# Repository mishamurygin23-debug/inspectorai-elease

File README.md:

# Инспектор ИИ — Стройнадзор Москвы

> **Интеллектуальная система автоматического контроля проектных решений, отслеживания изменений между стадиями проектирования (ПД, РД) и верификации исполнительной документации (ИД) по 132 параметрам Мосгосстройнадзора.**
> 
> *Решение разработано в рамках Задачи №10 для Комитета государственного строительного надзора города Москвы (Мосгосстройнадзор).*

---

## 📌 Содержание
1. [О проекте и назначение системы](#-о-проекте-и-назначение-системы)
2. [Ключевые возможности и функциональные модули](#-ключевые-возможности-и-функциональные-модули)
3. [Архитектура решения](#-архитектура-решения)
4. [Матрица 132 параметров контроля](#-матрица-132-параметров-контроля)
5. [ML-модели и пайплайн дообучения](#-ml-модели-и-пайплайн-дообучения)
6. [Интеграция с ИАС РИН и подписание УКЭП](#-интеграция-с-иас-рин-и-подписание-укэп)
7. [Ролевая модель доступа (RBAC)](#-ролевая-модель-доступа-rbac)
8. [Установка и запуск](#-установка-и-запуск)
9. [Структура проекта](#-структура-проекта)
10. [Сценарий работы инспектора (Quick Start)](#-сценарий-работы-инспектора-quick-start)

---

## 🏢 О проекте и назначение системы

При строительстве объектов капитального строительства в Москве возникает критический разрыв между:
1. **Проектной документацией (ПД)**, прошедшей государственную экспертизу (Мосгосэкспертиза);
2. **Рабочей документацией (РД)**, по которой генподрядчик непосредственно ведёт строительно-монтажные работы на площадке;
3. **Исполнительной документацией (ИД)** — актами освидетельствования скрытых работ (АОСР), исполнительными геодезическими схемами и паспортами материалов.

Несогласованные изменения (самовольное изменение марок бетона, уменьшение сечений арматуры, перенос несущих перегородок, изменение габаритов эвакуационных выходов) несут прямую угрозу конструктивной надежности и пожарной безопасности.

**«Инспектор ИИ»** автоматизирует труд государственного строительного инспектора, мгновенно находя расхождения и формируя юридически выверенные акты проверок и предписания с привязкой к нормативной базе (СП, ГОСТ, ПП РФ № 87, Градостроительный кодекс РФ).

---

## ✨ Ключевые возможности и функциональные модули

### 1. 📊 Мониторинг и Дашборд объектов (`Dashboard`)
- Централизованный обзор строящихся объектов Москвы с присвоением риск-статуса (**Зелёный**, **Жёлтый**, **Красный**).
- Сводная аналитика нарушений по категориям критичности (Критические, Значительные, Незначительные).
- Воронка обработки параметров: *Всего проверено -> Подтвержденные нарушения -> Кандидаты -> Норма подтверждена -> Требует пояснений*.

### 2. 🔍 Инспекционное рабочее пространство (`InspectionWorkspace`)
- **Двухоконный и трехоконный сравнительный просмотр** документов (ПД vs РД vs ИД).
- **Интерактивный Bounding Box / Overlay**: подсвечивание точных фрагментов чертежей и спецификаций с визуализацией расхождений.
- **Инструменты верификации инспектора**:
  - Принятие замечания (`Подтвердить нарушение`).
  - Отклонение с обязательным указанием нормативного кода причины:
    - `WRONG_REVISION` — Сравнение с неактуальной ревизией листа;
    - `APPROVED_CHANGE` — Согласованное изменение (лист согласования/разрешение на изменение);
    - `OCR_ERROR` — Ошибка оптического распознавания текста;
    - `ALIGNMENT_ERROR` — Ошибка совмещения слоев/осей;
    - `PARAMETER_NOT_APPLICABLE` — Параметр не применимым к данному конструктиву;
    - `EXCEED_TOLERANCE_ACCEPTABLE` — Отклонение в пределах допустимых допусков по СП;
    - `OTHER` — Иная обоснованная причина.

### 3. 📐 Парсинг штампов и чертежей (`DrawingParserTab`)
- Автоматическое распознавание основной надписи (штампа) по **ГОСТ Р 21.101-2020** (шифр объекта, раздел, стадия, номер листа, ревизия, фамилии разработчиков, ГИП).
- Определение масштаба, координатных осей и слоёв чертежей.
- Автоматическая классификация загружаемых документов (ПД, РД, ИД) на основе текстовых и графических признаков с точностью >98%.

### 4. 🧠 Генератор гипотез и коллизий (`HypothesisTab`)
- Интеллектуальный поиск скрытых коллизий методами:
  - **Логический анализ связей** (например, диаметр арматуры в КР vs спецификация);
  - **Семантический диссонанс** (расхождения в текстовых указаниях ПЗ и чертежах АР/КР);
  - **Нормативный аудит** (проверка на соответствие СП 63.13330, СП 16.13330, СП 1.13130, СП 118.13330);
  - **ML-паттерны** (предсказание типичных мест фальсификаций и ошибок генподрядчиков).
- Интерактивный конструктор гипотез для быстрого добавления инспектором новых проверочных шаблонов.

### 5. 📑 Реестр исполнительной документации (`ExecutiveDocumentationRegistry`)
- Электронный учет актов освидетельствования скрытых работ (АОСР) по РД-11-02-2006 / Приказу Минстроя № 344/пр.
- Контроль наличия геодезических исполнительных схем и паспортов/сертификатов на материалы (бетон, арматура, сэндвич-панели).
- Двусторонняя проверка: сверка объемов и дат в АОСР с общим журналом работ (РД-11-05-2007) и проектом.

### 6. 🏛 Интеграция с ИАС РИН Мосгосстройнадзора (`IaisRinTab`)
- Прямая синхронизация с **Информационно-аналитической системой управления контрольно-надзорной деятельностью (ИАС РИН)**.
- Формирование структурированных пакетов данных проверки (JSON/XML).
- Подписание актов проверки и предписаний **Усиленной квалифицированной электронной подписью (УКЭП)** инспектора по стандарту **ГОСТ Р 34.10-2012 / ГОСТ Р 34.11-2012**.

### 7. 🤖 ML-репозиторий и дообучение моделей (`MLRepositoryTab`, `MLRetrainingTab`)
- Управление версиями весов специализированных моделей (текущий рабочий чекпоинт `v2.4.2-altufievo-finetuned`).
- Формирование «Золотого датасета» (Gold Standard Ground Truth) на основе вердиктов экспертов-инспекторов.
- Пайплайн запуска дообучения (`fine_tune_pipeline.py`) с отслеживанием метрик в реальном времени.

### 8. 🛡 Неизменяемый журнал аудита WORM (`AuditLogTab`)
- Принцип **Write Once, Read Many (WORM)** для исключения фальсификации результатов проверок.
- Фиксация каждого действия (загрузка файла, подтверждение/отклонение замечания, подписание УКЭП, экспорт).
- Формирование криптографических хешей записей аудита для гарантии неизменности истории.

---

## 🏛 Архитектура решения

```
┌────────────────────────────────────────────────────────────────────────┐
│                   ФРОНТЕНД-ПРИЛОЖЕНИЕ (React 19 + TypeScript)          │
│                                                                        │
│  ┌──────────────┐  ┌──────────────────┐  ┌───────────────────────────┐ │
│  │  Дашборд     │  │  Инспекционное   │  │  Матрица 132 параметров   │ │
│  │  объектов    │  │  пространство    │  │  (ПП РФ № 87, СП, ГОСТ)   │ │
│  └──────┬───────┘  └─────────┬────────┘  └─────────────┬─────────────┘ │
│         │                    │                         │               │
│  ┌──────┴───────┐  ┌─────────┴────────┐  ┌─────────────┴─────────────┐ │
│  │ Парсер ГОСТ  │  │ Двухоконный PDF- │  │  Реестр ИД (АОСР, схемы,  │ │
│  │ штампов / CAD│  │ вьювер с BBox    │  │  лабораторные паспорта)   │ │
│  └──────┬───────┘  └─────────┬────────┘  └─────────────┬─────────────┘ │
│         │                    │                         │               │
│  ┌──────┴────────────────────┴─────────────────────────┴─────────────┐ │
│  │          Слой бизнес-логики и верификации нарушений               │ │
│  └──────┬────────────────────┬─────────────────────────┬─────────────┘ │
└─────────┼────────────────────┼─────────────────────────┼───────────────┘
          │                    │                         │
          ▼                    ▼                         ▼
┌──────────────────┐ ┌──────────────────┐ ┌──────────────────────────────┐
│  AI / ML Модуль  │ │   Криптография   │ │       Интеграция ИАС РИН     │
│  - OCR & Layout  │ │   и WORM-Аудит   │ │       Мосгосстройнадзора     │
│  - Cross-Doc Link│ │ - УКЭП           │ │ - Экспорт пакета проверки    │
│  - Поиск коллизий│ │   ГОСТ 34.10-2012│ │ - Синхронизация статусов     │
│  - Fine-tuning   │ │ - Хеш-цепочка    │ │ - Выгрузка предписаний в PDF │
└──────────────────┘ └──────────────────┘ └──────────────────────────────┘
```

---

## 📋 Матрица 132 параметров контроля

Система контролирует документацию по 132 утверждённым параметрам, сгруппированным по обязательным разделам проектной документации (согласно **Постановлению Правительства РФ № 87**):

| Шифр раздела | Наименование раздела ПД | Кол-во параметров | Примеры контролируемых параметров | Нормативная база |
|--------------|-------------------------|-------------------|-----------------------------------|-------------------|
| **ПЗ** | Пояснительная записка | 8 | ТЭПы, площадь застройки, этажность, класс энергоэффективности | ПП РФ № 87, СП 118.13330 |
| **СПЗУ** | Схема планировочной организации земельного участка | 12 | Границы ГПЗУ, красные линии, процент застройки, проезды МЧС | СП 42.13330, СП 4.13130 |
| **АР** | Архитектурные решения | 24 | Высотные отметки, ширина коридоров и выходов, огнестойкость ограждений | СП 54.13330, СП 1.13130 |
| **КР** | Конструктивные решения | 28 | Класс бетона, диаметр/шаг рабочей арматуры, глубина заложения свай | СП 63.13330, СП 22.13330 |
| **ИОС 1–5** | Инженерные сети (ЭОМ, ВК, ОВ, СС, ТС) | 32 | Нагрузки кВт, расходы воды, воздухообмен, пожаротушение, категории надежности | СП 30, 31, 60, 10, 134 |
| **ПОС / ПОД**| Проект организации строительства / сноса | 10 | Опасные зоны кранов, бытовой городок, мойка колес, стройгенплан | СП 48.13330 |
| **ППМ** | Мероприятия пожарной безопасности | 10 | Категории по взрывопожароопасности, противопожарные преграды | ФЗ № 123-ФЗ, СП 2.13130 |
| **ОДИ** | Доступность для маломобильных групп | 8 | Уклоны пандусов, ширина дверей, тактильные полосы, лифты | СП 59.13330.2020 |

Полная интерактивная таблица с формулами сопоставления, порогами допусков и источниками данных доступна во вкладке **«Матрица 132 параметров»**.

---

## 🧠 ML-модели и пайплайн дообучения

В состав системы входит специализированная мультимодальная архитектура для анализа строительной документации:
- **Детекция и извлечение таблиц и штампов:** Выделение зон основных надписей по ГОСТ 21.101-2020.
- **Cross-Document Entity Linking:** Связывание позиций между ведомостями расхода стали, планами армирования и паспортами качества свай.
- **Модель детекции нарушений (`inspector_hypothesis_v2.4`):**
  - Обучена и валидирована на реальном комплекте документации г. Москвы (*Торговое здание, Алтуфьевское шоссе, вл. 79Б, стр. 1*).
  - **Character Accuracy (OCR):** 98.8%
  - **Exact Match (марки материалов):** 95.2%
  - **BBox IoU (точность локализации):** 97.2%
  - **Precision:** 98.2%
  - **Recall:** 94.5%
  - **Интегральный F1-score:** 96.8%

Запуск переобучения пайплайна:
```bash
python ml_models/inspector_hypothesis_v2.4/fine_tune_pipeline.py --epochs 5 --dataset dataset_altufievo_ground_truth.json
```

---

## 🔒 Интеграция с ИАС РИН и подписание УКЭП

1. **Формирование дела проверки:** Агрегация всех подтвержденных инспектором нарушений, доказательных фрагментов (BBox-полигонов) и ссылок на листы ПД/РД/ИД.
2. **Криптографическое подписание:**
   - Поддерживаются сертификаты квалифицированной электронной подписи по стандартам **ГОСТ Р 34.10-2012** (длина ключа 256/512 бит) и **ГОСТ Р 34.11-2012**.
   - Формирование отсоединенной или присоединенной подписи (форматы CMS/CAdES-BES).
3. **Шлюз взаимодействия с ИАС РИН:**
   - Передача пакета через защищенный REST/SOAP API с присвоением входящего номера и трекингом статуса проверки в режиме онлайн.

---

## 👥 Ролевая модель доступа (RBAC)

Система поддерживает 4 базовые роли с разграничением прав:
1. **Инспектор Мосгосстройнадзора (`INSPECTOR`):**
   - Загрузка проектной, рабочей и исполнительной документации.
   - Проведение проверок, верификация гипотез (подтверждение/отклонение нарушений).
   - Подписание предписаний личной УКЭП.
2. **Супервайзер / Начальник управления (`SUPERVISOR`):**
   - Контроль работы подведомственных инспекторов.
   - Утверждение предписаний высокой степени опасности.
   - Сквозной мониторинг строительных объектов Москвы.
3. **ML-инженер / Аналитик данных (`ML_ENGINEER`):**
   - Мониторинг метрик распознавания и детекции коллизий.
   - Формирование эталонных выборок и запуск дообучения моделей.
   - Управление репозиторием чекпоинтов.
4. **Администратор системы (`ADMIN`):**
   - Управление справочниками нормативной базы (СП, ГОСТ, приказы).
   - Настройка интеграций с ИАС РИН.
   - Контроль целостности WORM-журнала аудита.

---

## 🚀 Установка и запуск

### Системные требования
- **Node.js:** версия 18.0 или выше (рекомендуется 20 LTS)
- **Менеджер пакетов:** npm, pnpm или bun
- **Python (для ML-пайплайна дообучения):** 3.10+ с установленными `torch`, `transformers`

### Пошаговая инструкция

1. **Клонирование репозитория:**
   ```bash
   git clone <URL_РЕПОЗИТОРИЯ>
   cd inspector-ai-stroynadzor
   ```

2. **Установка зависимостей фронтенда:**
   ```bash
   npm install
   ```

3. **Запуск сервера разработки:**
   ```bash
   npm run dev
   ```
   Приложение откроется по адресу `http://localhost:3000`.

4. **Проверка типов и линтинг:**
   ```bash
   npm run lint
   ```

5. **Сборка для промышленного развертывания (Production build):**
   ```bash
   npm run build
   ```
   Собранное статическое приложение размещается в каталоге `dist/`.

6. **Предпросмотр production-сборки:**
   ```bash
   npm run preview
   ```

---

## 📂 Структура проекта

```
.
├── index.html                   # HTML-шаблон с метаданными и шрифтами
├── package.json                 # Зависимости и npm-скрипты (Vite, React 19, Tailwind CSS)
├── vite.config.ts               # Конфигурация сборщика Vite
├── tsconfig.json                # Параметры компилятора TypeScript
├── metadata.json                # Метаданные приложения и права доступа
├── ml_models/                   # Репозиторий весов и скриптов ML-моделей
│   └── inspector_hypothesis_v2.4/
│       ├── config.json          # Параметры архитектуры нейросети
│       ├── dataset_altufievo_ground_truth.json # Размеченный золотой датасет
│       ├── fine_tune_pipeline.py # Скрипт дообучения
│       ├── model_metadata.json  # Метрики точности и версии
│       └── README.md            # Отчет по валидации модели
├── docs/                        # Расширенная техническая документация
│   ├── ARCHITECTURE.md          # Детальная архитектура и потоки данных
│   ├── USER_GUIDE.md            # Руководство пользователя для инспекторов
│   └── API_AND_INTEGRATION.md   # Спецификация обмена с ИАС РИН
└── src/
    ├── main.tsx                 # Точка входа React
    ├── App.tsx                  # Главный компонент, роутинг вкладок и глобальное состояние
    ├── index.css                # Глобальные стили Tailwind CSS
    ├── types/                   # TypeScript интерфейсы и типы данных
    │   ├── index.ts             # Типы объектов, проверок, гипотез, статусов
    │   └── sectionsRegistry.ts  # Реестр разделов ПП РФ № 87
    ├── data/                    # Базы данных и справочники
    │   ├── matrix132.ts         # Матрица 132 параметров Мосгосстройнадзора
    │   ├── mockData.ts          # Демонстрационные объекты, протоколы и логи
    │   ├── comprehensiveHypothesesData.ts # База типовых нарушений и коллизий
    │   └── rolesData.ts         # Профили пользователей и уровни доступа
    ├── components/              # Реакт-компоненты модулей системы
    │   ├── Navbar.tsx           # Верхняя панель навигации и переключение ролей
    │   ├── Dashboard.tsx        # Дашборд объектов и аналитики
    │   ├── InspectionWorkspace.tsx # Рабочее место верификации инспектора
    │   ├── ActualPdfViewer.tsx  # Просмотрщик PDF с интерактивными оверлеями
    │   ├── DrawingParserTab.tsx # Модуль парсинга штампов по ГОСТ 21.101-2020
    │   ├── HypothesisTab.tsx    # Генератор и база гипотез коллизий
    │   ├── ExecutiveDocumentationRegistry.tsx # Реестр исполнительной документации
    │   ├── Matrix132Tab.tsx     # Просмотр и фильтрация матрицы 132 параметров
    │   ├── IaisRinTab.tsx       # Интеграция с ИАС РИН и подписание УКЭП
    │   ├── MLRepositoryTab.tsx  # Управление ML-моделями и метриками
    │   ├── MLRetrainingTab.tsx  # Дообучение моделей на размеченных данных
    │   ├── NormativeBaseTab.tsx # Справочник СП, ГОСТ, законов РФ
    │   ├── AuditLogTab.tsx      # Журнал неизменяемого WORM-аудита
    │   ├── UploadModal.tsx      # Мастер загрузки документации (ПД/РД/ИД)
    │   ├── ExportModal.tsx      # Мастер экспорта предписаний и актов
    │   ├── CreateObjectModal.tsx # Создание нового строительного объекта
    │   └── AuthModal.tsx        # Модальное окно авторизации и смены ролей
    └── utils/                   # Вспомогательные утилиты
        ├── documentClassifier.ts # Автоматическая классификация документов
        ├── reportGenerator.ts   # Генерация официальных актов и отчетов
        └── samplePdfGenerator.ts # Генерация тестовых PDF-чертежей
```

---

## 🛠 Сценарий работы инспектора (Quick Start)

1. **Создание объекта строительства:**
   - Нажмите кнопку **«+ Создать объект»** в верхнем меню.
   - Заполните наименование объекта, адрес, номер разрешения на строительство (РНС), реквизиты заказчика и подрядчика.
2. **Загрузка документации:**
   - Нажмите кнопку **«Загрузить ПД / РД / ИД»**.
   - Перетащите PDF-файлы проектной, рабочей или исполнительной документации.
   - Умный классификатор автоматически определит стадию документа, раздел по ПП РФ № 87 и реквизиты штампа ГОСТ.
3. **Верификация нарушений в «Рабочем месте инспектора»:**
   - Перейдите на вкладку **«Верификация протокола»**.
   - В левом списке выберите проверяемый параметр (например, *«КР-55. Класс бетона монолитных ростверков»*).
   - В центральной области просмотрите подсвеченные доказательные фрагменты (ПД vs РД vs ИД).
   - Примите решение:
     - Нажмите **«Подтвердить нарушение»** для включения в проект предписания;
     - Либо нажмите **«Отклонить замечание»** с выбором обоснования из выпадающего списка (например, *«Согласованное изменение»*).
4. **Формирование и подписание предписания:**
   - Перейдите на вкладку **«Интеграция ИАС РИН»**.
   - Ознакомьтесь с автоматически сформированным проектом Предписания об устранении нарушений.
   - Вставьте ключевой носитель (Рутокен/JaCarta) и нажмите **«Подписать УКЭП инспектора»**.
   - Нажмите **«Синхронизировать с ИАС РИН»** — делу проверки будет присвоен уникальный входящий номер в государственной системе.
5. **Экспорт отчетности:**
   - Нажмите **«Экспорт»** на панели инструментов для скачивания официального акта проверки в формате PDF, реестра несоответствий в Excel или машиночитаемого пакета XML/JSON.

---

## ⚖️ Лицензия и правовая информация
Разработано для применения в органах государственного строительного надзора г. Москвы. Все права защищены (2026). Соответствует требованиям Федерального закона № 214-ФЗ, Федерального закона № 123-ФЗ, Градостроительного кодекса РФ и нормам цифровизации Мосгосстройнадзора.

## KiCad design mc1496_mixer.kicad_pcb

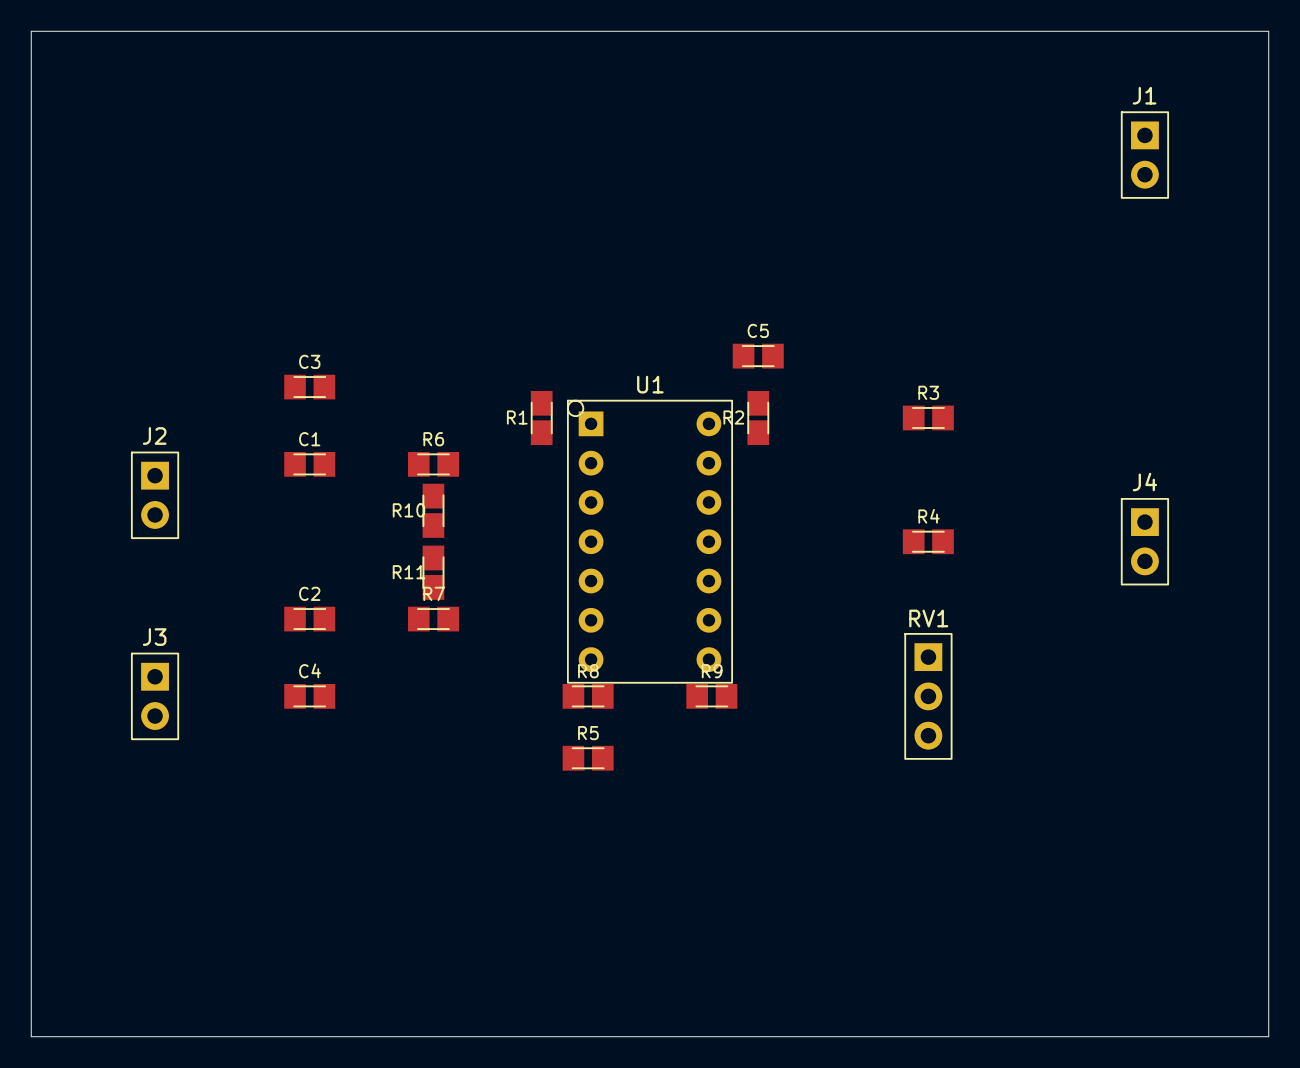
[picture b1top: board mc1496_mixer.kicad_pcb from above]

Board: 2 copper layers, 80.0 x 65.0 mm, 22 parts (0 on the bottom side), 13 nets, no tracks yet.

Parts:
C1, C2, C3, C4: 100n; C_0805_2012Metric
C5: 10n; C_0805_2012Metric
J1: VCC+GND; PinHeader_1x002_P2.54mm_Vertical
J2: Carrier; PinHeader_1x002_P2.54mm_Vertical
J3: Signal; PinHeader_1x002_P2.54mm_Vertical
J4: Output; PinHeader_1x002_P2.54mm_Vertical
R1, R2: 3.9k; R_0805_2012Metric
R3, R4: 6.8k; R_0805_2012Metric
R5: 750; R_0805_2012Metric
R6, R7: 51; R_0805_2012Metric
R8, R9: 1k; R_0805_2012Metric
R10, R11: 10k; R_0805_2012Metric
RV1: 50k; PinHeader_1x003_P2.54mm_Vertical
U1: MC1496; DIP-14_W7.62mm

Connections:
BIAS5: R5.1, U1.5
CARRIER_BIAS: R3.2, R4.1, RV1.1, RV1.3
CARRIER_N: C2.1, C2.2, J2.2, R7.1, R7.2, U1.10
CARRIER_P: C1.1, C1.2, J2.1, R6.1, R6.2, U1.8
GND: C5.2, J1.2, R5.2, R8.2, R9.2, U1.7
OUT_N: J4.2, R2.1, U1.12
OUT_P: J4.1, R1.1, U1.6
RE1: R8.1, U1.2
RE2: R9.1, U1.3
SIGNAL_BIAS: R4.2, R10.1, R11.1
SIGNAL_N: C3.1, C3.2, J3.2, R10.2, U1.1
SIGNAL_P: C4.1, C4.2, J3.1, R11.2, U1.4
VCC: C5.1, J1.1, R1.2, R2.2, R3.1, U1.14
